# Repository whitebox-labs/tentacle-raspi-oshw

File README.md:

# The Tentacle T3 for Raspberry Pi

These are the hardware source files for the Tentacle T3 - an add-on board for Raspberry Pi to interface with Atlas Scientific sensor circuits.

Full documentation is here: https://www.whiteboxes.ch/tentacle

If you find bug in the examples or the schematic, feel free to create an issue or even a pull request here on GitHub. For help and user support, please use the form on our website.

License of pcb schematics and layout: http://creativecommons.org/licenses/by-sa/4.0/
Licence: https://creativecommons.org/licenses/by-sa/4.0/
Creative Commons Attribution-ShareAlike 4.0 International

Silkscreen graphics and the trade mark "Tentacle T3" are intellectual property of Whitebox Labs (please create your own graphics ;)).

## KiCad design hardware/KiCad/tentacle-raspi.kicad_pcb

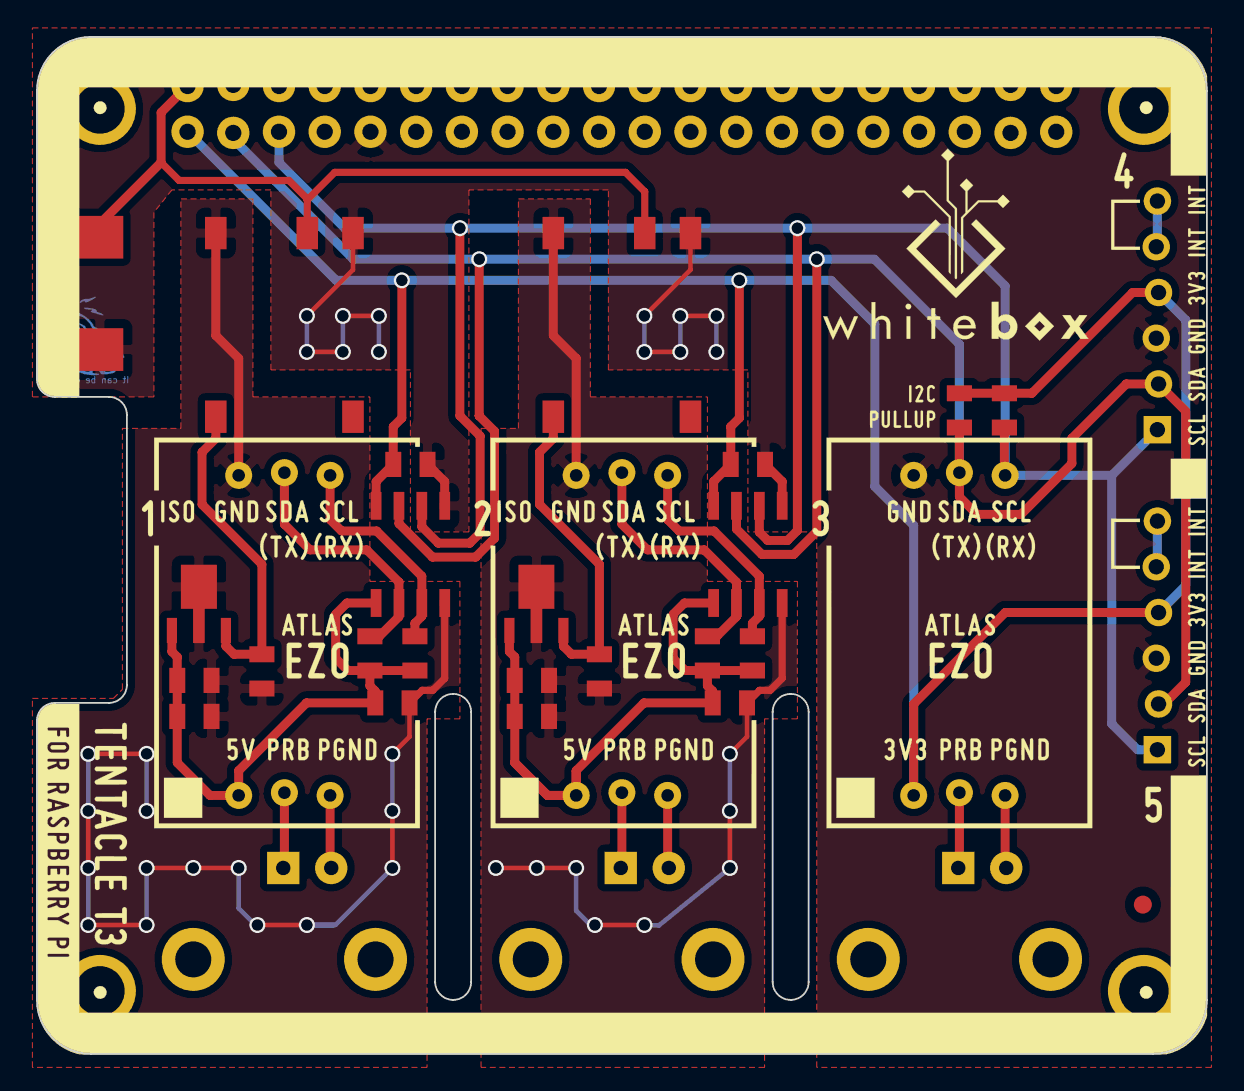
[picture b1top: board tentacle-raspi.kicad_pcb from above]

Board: 2 copper layers, 65.0 x 56.5 mm, 37 parts (1 on the bottom side), 23 nets.

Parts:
BOT: LOGO; WL-BOT-T3
C101: 470µF; WL-CASE-X-2917
C201, C202, C301, C302: 1µF; WL-SM0805C
C203, C303: 2.2µF; WL-SM0805C
C204, C205, C304, C305: 0.1 µF; WL-SM0805C
DCDC201, DCDC301: R1SE_0505; WL-R1SE-0505
P101, P102: CONN_01X06; WL-PINH_1X6_snk
P201, P301, P401: BNC; WL-EB08040502_snk
PI_BOARD101: RASPBERRY_PI_2; WL-40pin_snk
PI_Board: VAL**; WL-PI_Board_no_outline
R101, R102, R201, R202, R301, R302: 4.7K; WL-SM0805R
REG201, REG301: LD2981ABU50TR; WL-SOT89
SIG_ISO201, SIG_ISO301: SI8600; WL-SOIC8N
STP201, STP301, STP401: ATLAS_STAMP; WL-ezo-19454_snk
TOP: LOGO; WL-TOP-T3
fiducial: VAL**; WL-fiducial_1mm
fiducial#2: VAL**; WL-fiducial_1mm

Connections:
+3.3V: C205.1, C305.1, P101.4, P102.4, PI_BOARD101.1, R101.2, R102.2, SIG_ISO201.8, SIG_ISO301.8, STP401.4
/SCL: P101.1, P102.1, PI_BOARD101.5, R102.1, SIG_ISO201.6, SIG_ISO301.6, STP401.3
/SDA: P101.2, P102.2, PI_BOARD101.3, R101.1, SIG_ISO201.7, SIG_ISO301.7, STP401.2
GND: C101.2, C205.2, C305.2, DCDC201.1, DCDC301.1, P101.3, P102.3, PI_BOARD101.9, SIG_ISO201.5, SIG_ISO301.5, STP401.1
GND_ISO2: C201.1, C202.1, C203.1, C204.1, DCDC201.4, REG201.2, SIG_ISO201.4, STP201.1
GND_ISO3: C301.1, C302.1, C303.1, C304.1, DCDC301.4, REG301.2, SIG_ISO301.4, STP301.1
unnamed: C202.2, DCDC201.5, REG201.3
unnamed: C302.2, DCDC301.5, REG301.3
unnamed: P101.5, P101.6
unnamed: P102.5, P102.6
unnamed: P201.1, STP201.5
unnamed: P201.2, STP201.6
unnamed: P301.1, STP301.5
unnamed: P301.2, STP301.6
unnamed: P401.1, STP401.5
unnamed: P401.2, STP401.6
unnamed: R201.2, SIG_ISO201.3, STP201.3
unnamed: R202.2, SIG_ISO201.2, STP201.2
unnamed: R301.2, SIG_ISO301.3, STP301.3
unnamed: R302.2, SIG_ISO301.2, STP301.2
VCC: C101.1, DCDC201.2, DCDC301.2, PI_BOARD101.2
V_ISO2: C201.2, C203.2, C204.2, R201.1, R202.1, REG201.1, SIG_ISO201.1, STP201.4
V_ISO3: C301.2, C303.2, C304.2, R301.1, R302.1, REG301.1, SIG_ISO301.1, STP301.4

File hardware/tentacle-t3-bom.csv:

Id,Description,Package,Qty,Designator,Designation
1,2x40-pin female header .1inch,.1 inch header,1,PI_BOARD101,RASPBERRY_PI_2
2,LDO voltage regulator,SOT89,2,"REG201,REG301",LD2981ABU50TR
3,Digital signal isolator,SOIC-8,2,"SIG_ISO201, SIG_ISO301",SI8600
4,"SMD resistor 4.7K, 1/8W",SM0805,6,"R101, R102, R201, R202, R301, R302",4.7K
5,Multilayer Ceramic Capacitor 0.1uF,SM0805,4,"C204, C205, C304, C305",0.1 µF
6,Multilayer Ceramic Capacitor 1uF,SM0805,4,"C201, C202, C301, C302",1µF
7,Multilayer Ceramic Capacitor 2.2uF,SM0805,2,"C203, C303",2.2µF
8,Tantalum Capacitor 470uF,C_TANT_CASE_X,1,C101,470µF
9,Isolated DC/DC converter 5V,R1SE_0505,2,"DCDC201,DCDC301",R1SE_0505
10,BNC Connector,BNC-1337542,3,"P201,P301",BNC
11,1x3-pin female header .1inch,1x3  .1 inch spacing female pin,6,"STP201,STP301",ATLAS_STAMP
12,1x6-pin male header .1inch,1x6 .1 inch spacing male pin,2,"P101, P102",CONN_01X06

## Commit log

2017-08-21 Initial commit / publication
2017-08-21 updated 2d-drawing
2018-08-26 add STEP file (3D model)
2018-09-21 zipped STEP model for easier download
